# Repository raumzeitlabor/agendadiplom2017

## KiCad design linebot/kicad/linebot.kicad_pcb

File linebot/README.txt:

# LineBot

## Allgemeine Tipps

In einem sehr hellen Raum hat der Bot Schwierigkeiten, die Linien zu finden.
Deshalb etwas abdunkeln. Du kannst auch eine hellere LED einlöten. Außerdem
müssen die gemalten Linien recht breit sein. Also einen dicken Edding nehmen,
oder ein dunkles Klebeband. Der Bot hat keine Reifen, nur ein kleines Stück
Schrumpfschlauch auf den Achsen. Falls der sich gelöst hat, kommt der Bot nicht
mehr richtig um die Kurve. Dann einfach noch ein bisschen den Schrumpfschlauch
erhitzen, z.B. mit einem Feuerzeug.

## Bauanleitung

> Sicherheitshinweise
> 
> Lötzinn enthält Blei; das ist nicht gesund, wenn man es verschluckt. Wasch
> Dir deshalb nach dem Löten gründlich die Hände. Während des Arbeitens mit dem
> Lötkolben solltest Du nicht mit Lebensmitteln hantieren oder essen.
> 
> Der Lötkolben hat an seiner Spitze eine Temperatur von ca. 300 bis 350°C,
> genug um bestimmte Metalle zu schmelzen. Gib deshalb besonders Acht, Dich und
> andere nicht zu verletzen und stelle den Lötkolben immer in die Halterung,
> wenn Du ihn gerade nicht benötigst.
> 
> Halte überstehende Drahtenden fest, wenn Du sie abzwickst. So kannst Du
> vermeiden, dass die Teile wegspringen und Dich oder jemanden in Deiner
> Umgebung treffen.

Eine Platine hat normalerweise Symbole aufgedruckt, welche Bauteile man an
einer bestimmten Stelle einsetzen muss. 
Widerstände sind mit Rechtecken dargestellt und einem Wert, der mit R beginnt.
Zum Beispiel bedeutet R3: an diese Stelle gehört der Widerstand (engl.
Resistor) Nummer drei.

Die Abstände der einzelnen Kontakte haben meistens einen festen Wert, der sich
am amerikanischen Einheitensystem orientiert. Bauteile, z.B. Kondensatoren,
Widerstände, passen genau in die Platine hinein, wenn Du die Drähte mit einer
Biege-Lehre gleichmäßig umbiegst.
Damit die Teile nicht wieder herausfallen, wenn Du die Platine zum Löten
umdrehst, kannst Du die Beinchen ein wenig auseinanderbiegen.

Das Löten klappt prima, wenn Du Dich an eine einfache Reihenfolge hälst:
Lötkolben dran, Lötzinn dran, Lötzinn weg, Lötkolben weg.
Wenn Du alles richtig gemacht hast, ist das Lötzinn geschmolzen und hat um die
Kontaktstelle einen etwa kegelförmigen Hügel gebildet.

Als erstes löten wir den Elektrolytkondensator C1 auf der Unterseite der
Platine ein.
Achte darauf, das Bauteil richtig herum einzusetzen. Auf der Seite mit dem
Pluspol ist eine Kerbe, die auch auf der Platine eingezeichnet ist.
Ein Elektrolytkondensator wirkt wie eine kleine Batterie. In unserer Schaltung
ist er dazu da, Spannungsschwankungen abzufangen, wenn die Motoren anlaufen.

Nun kommt der Sockel für den Microcontroller. Er hat an einer Seite eine Kerbe,
damit man ihn richtig herum einbaut. Beginne das Löten mit einer Ecke.
Kontolliere dann, ob das Bauteil gut sitzt. Dann kommt die diagonal
gegenüberliegende Ecke dran. Wenn der Sockel fest und gerade auf der Platine
sitzt, kannst Du auch die restlichen Kontakte festlöten.
Stecke dann den Microcontroller auf den Sockel. Eine Ecke ist mit einem Punkt
markiert. Die muss dort hin, wo auf der Platine eine 1 steht.
Der Microcontroller ist ein ATTiny85. Er ist das Gehirn unseres Roboters. Dort
kommen die Messwerte aus den Sensoren an und die Motoren bekommen von dort ihre
Steuersignale.

Jetzt löten wir alle fünf Widerstände fest. Die Richtung ist bei einem
Widerstand nicht wichtig aber der Wert muss stimmen. Jeder Widerstand hat einen
Code aus farbigen Ringen aufgedruckt. Achte darauf, dass Du die Widerstände in
Deinem Roboter-Bausatz nicht durcheinander bringst. Wenn Du Dir nicht sicher
bist, kannst Du den Wert des Widerstandes mit dem Multimeter nachmessen.
Widerstände sind zum Beispiel dazu da, den Strom in der Schaltung zu begrenzen,
damit andere Bauteile nicht kaputt gehen.

Die zwei kleinen Dioden sind als nächstes dran. Diesmal ist es wichtig, sie
richtig herum einzubauen. Dafür haben sie auf einer Seite einen schwarzen
Strich. In unserer Schaltung sind sie dafür zuständig, die Spannung der Motoren
abzufangen, die den Rest der Schaltung durcheinanderbringen würde.

Nun kommen die Transistoren dran. Sie haben eine flache und eine runde Seite,
damit man weiß, wie man sie einbauen muss. Die Beinchen der Transistoren sind
sehr dicht zusammen. Gib darauf acht, dass Du die Kontakte auf der Platine
nicht mit zu viel Lötzinn verbindest.
Transistoren funktionieren wie eine Schleuse: Wenn an der Basis (hier in der
Mitte) ein kleiner Steuerstrom anliegt, dann öffnen sie die Verbindung und
lassen den Strom durch. Wir brauchen Sie zum Ansteuern der Motoren.

Der Schalter hat drei Kontakte in der Mitte, die Du anlöten musst. Die beiden
Pfosten helfen, dass der Schalter besser auf der Platine hält und Du musst Sie
nicht anlöten.
Mit dem Schalter kannst Du den Bot ausschalten, wenn Du ihn gerade nicht auf
Liniensuche schicken willst.

Die Leuchtdiode (LED - Light Emitting Diode) kommt auf die Unterseite der
Platine. Sie funktioniert nur, wenn Du sie richtig herum einbaust. Die
abgeflachte Seite der LED ist eingezeichnet. Jetzt wird es ein bisschen
komplizierter. Die beiden Fototransistoren haben auch eine flache Seite. Sie
werden aber nicht direkt eingesetzt, sondern mit einer Halterung, die genau
darüber passt. Achte darauf, dass die Fototransistoren richtig herum sind und
drücke sie ganz in das Gehäuse hinein, bevor Du alles anlötest. Die Beinchen
der Transistoren kannst Du abzwicken. Aber wirf sie nicht weg, wir brauchen sie
im nächsten Schritt.
Die Fototransistoren sind der Sensor unseres Roboters. Sie lassen mehr Strom
durch, wenn mehr Licht einfällt. Das Licht kommt in diesem Fall von der LED und
wird dann von der Oberfläche des Tisches reflektiert. Eine dunkle Linie
reflektiert nicht so viel Licht und wird deshalb von den Sensoren erkannt.

Als Antrieb für unseren Roboter dienen zwei kleine Elektromotoren. Zur Montage
schiebst Du sie in die Halterung aus Kunststoff, bedruckte Seite in Richtung
Schlitz. Die Kontaktbeinchen kommen durch die Ösen der Halterung und werden
direkt am Motor angelötet. Biege die Kontakte so, dass sie senkrecht zur
Bodenfläche stehen und löte die Motoren auf der Platine fest.
Die Motoren sind sehr klein und haben nur ein geringes Drehmoment. Deshalb
bekommt unser Bot keine großen Reifen.

Als letztes wird die Batteriehalterung angelötet. Wenn Du nun die Batterien
einsetzt und den Schalter anstellst sollte der Bot losfahren. Viel Spaß!

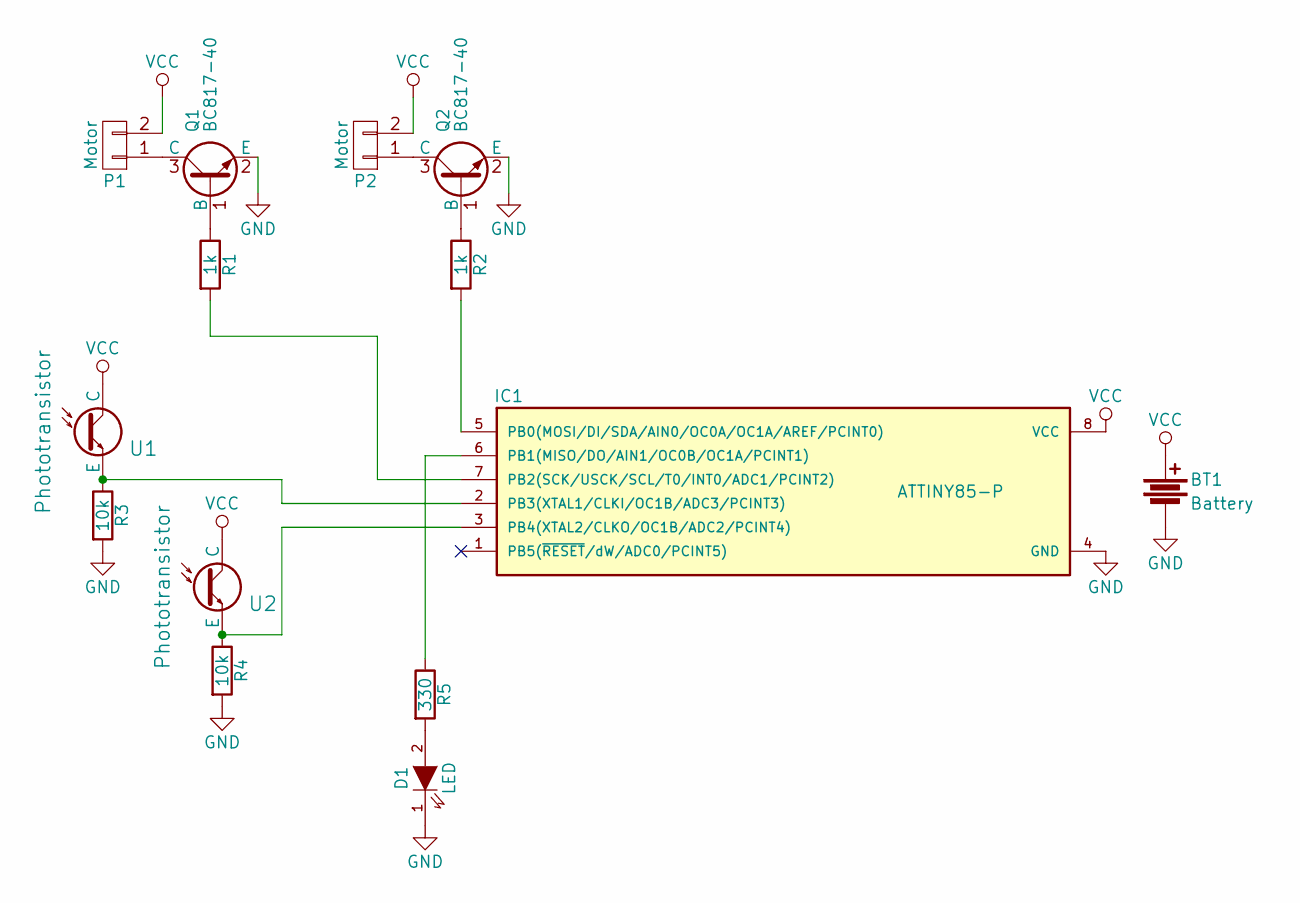
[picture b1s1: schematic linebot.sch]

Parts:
BT1: Battery; batteryholder_AAAx2
D1: LED; LED-5MM
IC1: ATTINY85-P; DIP-8_W7.62mm
P1, P2: Motor; motorholder
Q1, Q2: BC817-40; TO-92_Inline_Narrow_Oval
R1, R2: 1k; Resistor_Horizontal_RM10mm
R3, R4: 10k; Resistor_Horizontal_RM10mm
R5: 330; Resistor_Horizontal_RM10mm
U1, U2: Phototransistor; LED-5MM

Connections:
GND: BT1.2, D1.1 (K), IC1.4 (GND), Q1.2 (E), Q2.2 (E), R3.2, R4.2
unnamed: D1.2 (A), R5.2
unnamed: IC1.2 (PB3(XTAL1/CLKI/OC1B/ADC3/PCINT3)), R3.1, U1.2 (E)
unnamed: IC1.3 (PB4(XTAL2/CLKO/OC1B/ADC2/PCINT4)), R4.1, U2.2 (E)
unnamed: IC1.5 (PB0(MOSI/DI/SDA/AIN0/OC0A/OC1A/AREF/PCI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), R2.2
unnamed: IC1.6 (PB1(MISO/DO/AIN1/OC0B/OC1A/PCINT1)), R5.1
unnamed: IC1.7 (PB2(SCK/USCK/SCL/T0/INT0/ADC1/PCINT2)), R1.2
unnamed: P1.1, Q1.3 (C)
unnamed: P2.1, Q2.3 (C)
unnamed: Q1.1 (B), R1.1
unnamed: Q2.1 (B), R2.1
VCC: BT1.1, IC1.8 (VCC), P1.2, P2.2, U1.1 (C), U2.1 (C)

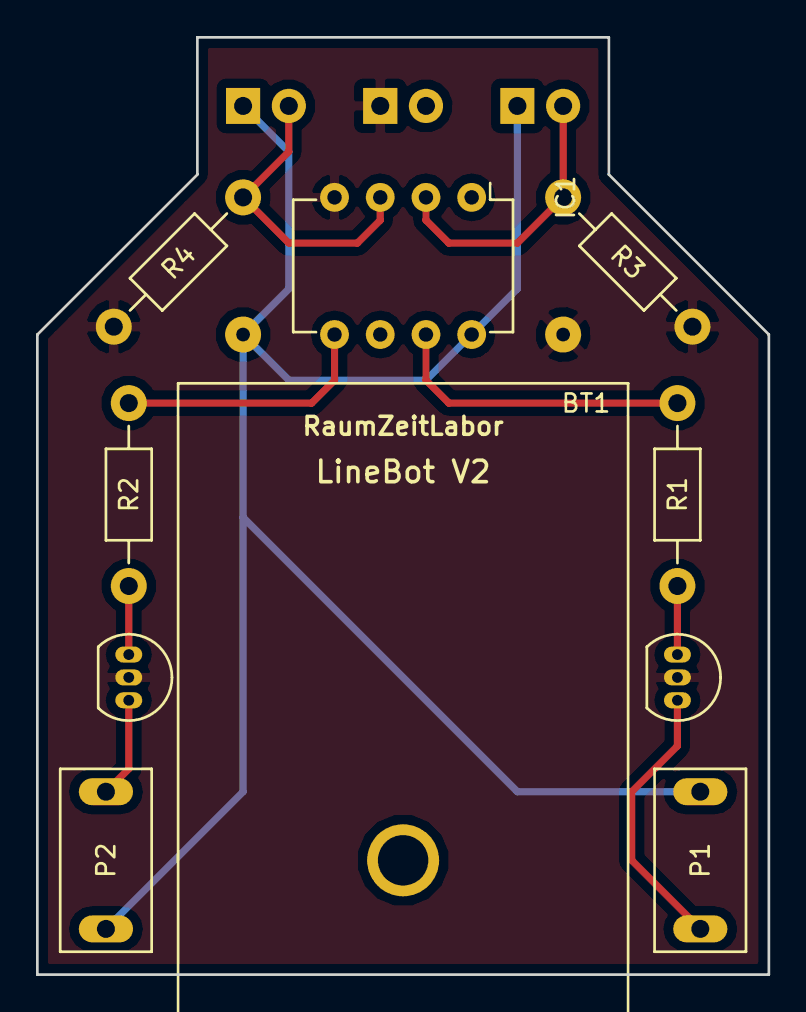
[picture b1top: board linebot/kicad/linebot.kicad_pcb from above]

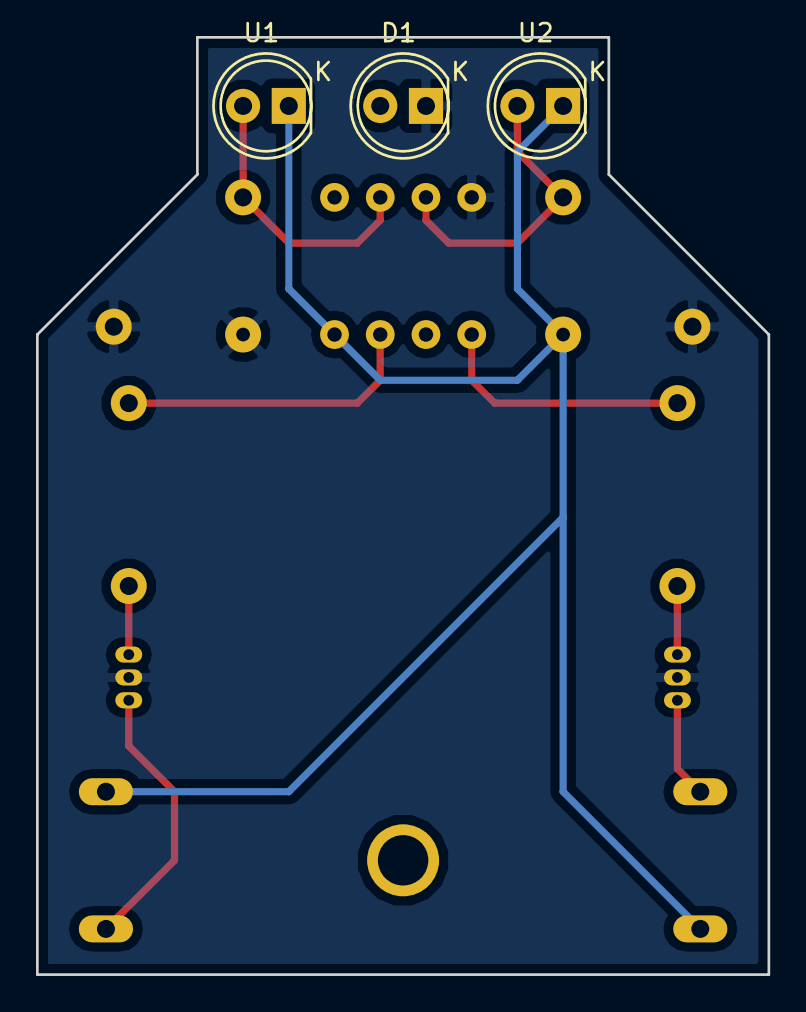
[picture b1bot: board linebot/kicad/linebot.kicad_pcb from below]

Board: 2 copper layers, 40.6 x 52.1 mm, 13 parts (3 on the bottom side), 10 nets.

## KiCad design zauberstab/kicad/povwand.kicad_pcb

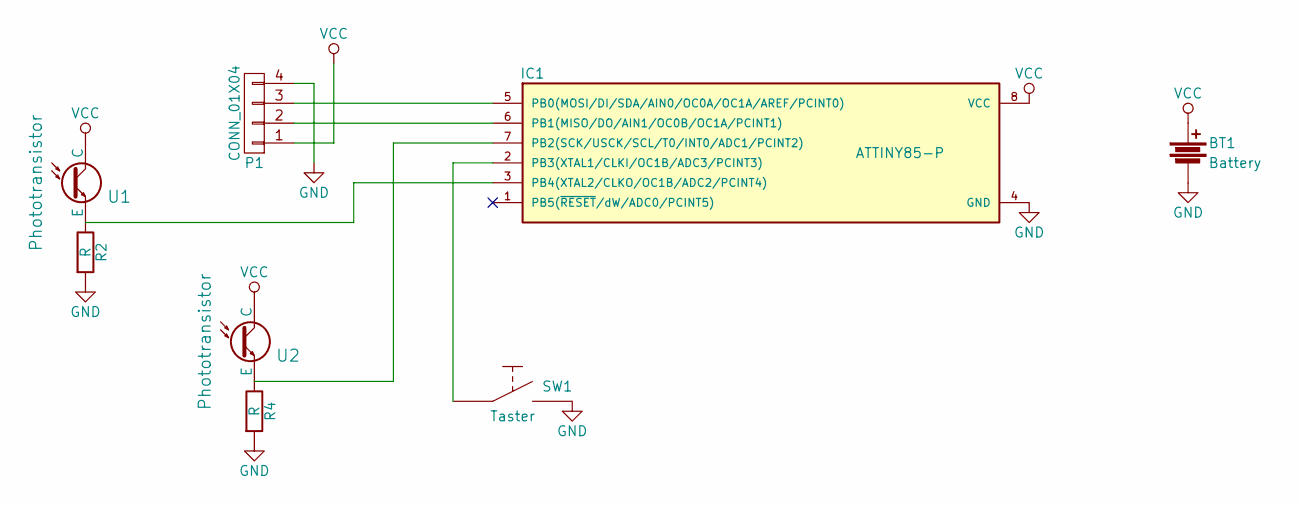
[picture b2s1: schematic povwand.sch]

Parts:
BT1: Battery; 2xAAAbattery_holder_long
IC1: ATTINY85-P; DIP-8_W7.62mm
P1: CONN_01X04; APA102x8
R2, R4: R; Resistor_Horizontal_RM10mm
SW1: Taster; Kurzhubtaster
U1, U2: Phototransistor; LED-5MM

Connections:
GND: BT1.2, IC1.4 (GND), P1.4, R2.2, R4.2, SW1.2
unnamed: IC1.2 (PB3(XTAL1/CLKI/OC1B/ADC3/PCINT3)), SW1.1
unnamed: IC1.3 (PB4(XTAL2/CLKO/OC1B/ADC2/PCINT4)), R2.1, U1.2 (E)
unnamed: IC1.5 (PB0(MOSI/DI/SDA/AIN0/OC0A/OC1A/AREF/PCI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), P1.3
unnamed: IC1.6 (PB1(MISO/DO/AIN1/OC0B/OC1A/PCINT1)), P1.2
unnamed: IC1.7 (PB2(SCK/USCK/SCL/T0/INT0/ADC1/PCINT2)), R4.1, U2.2 (E)
VCC: BT1.1, IC1.8 (VCC), P1.1, U1.1 (C), U2.1 (C)

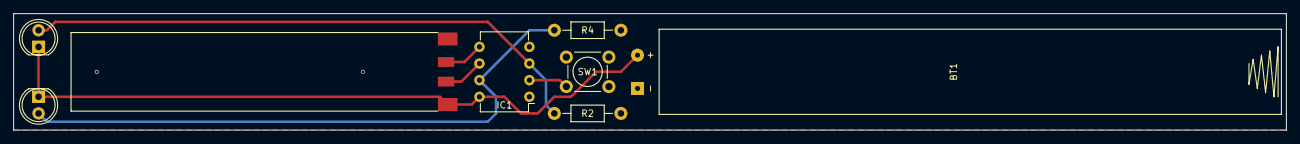
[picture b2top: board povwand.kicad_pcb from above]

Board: 2 copper layers, 194.3 x 17.8 mm, 8 parts (0 on the bottom side), 7 nets.

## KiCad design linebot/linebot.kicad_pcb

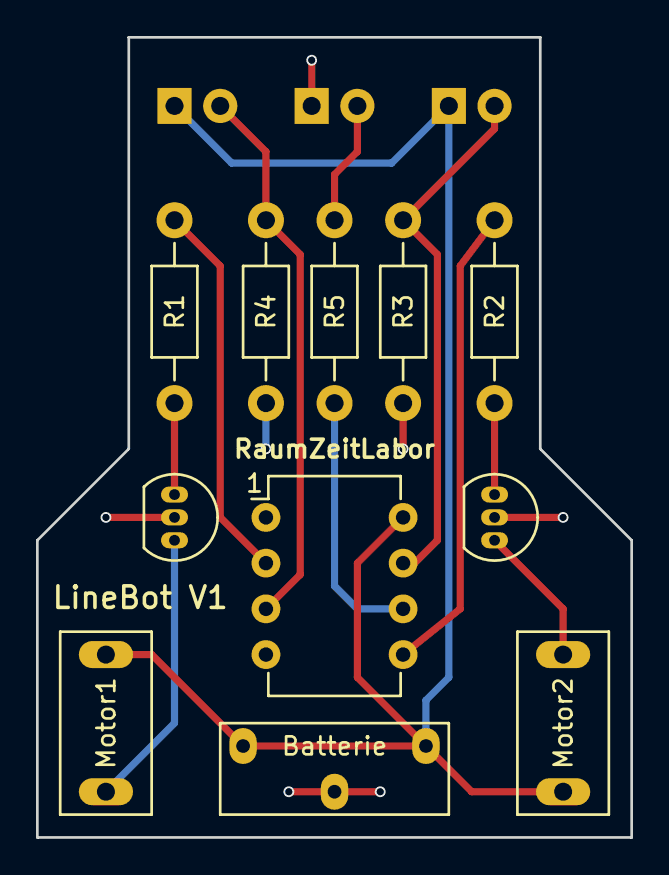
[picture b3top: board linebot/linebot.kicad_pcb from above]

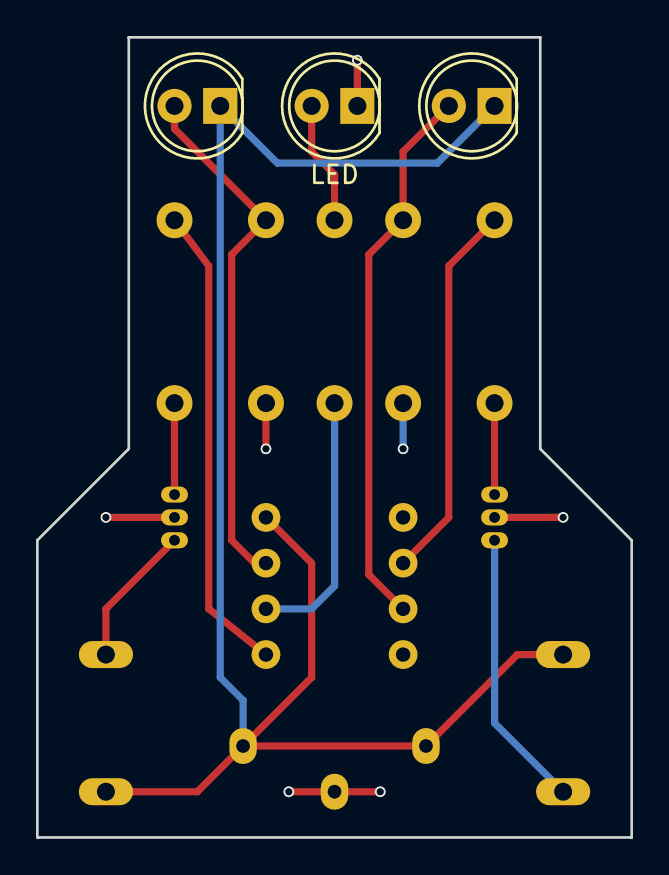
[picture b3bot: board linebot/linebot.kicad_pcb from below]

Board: 2 copper layers, 33.0 x 44.4 mm, 14 parts (3 on the bottom side), 12 nets.

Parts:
1: ATTINY85-P; DIP-8_W7.62mm
Batterie: Battery; Batterie_aufrecht
LED: LED; LED-5MM
Motor1, Motor2: Motor; motorholder
Q1, Q2: BC817-40; TO-92_Inline_Narrow_Oval
Q3, Q4: PT; LED-5MM
R1, R2: 1k; Resistor_Horizontal_RM10mm
R3, R4: 10k; Resistor_Horizontal_RM10mm
R5: 330; Resistor_Horizontal_RM10mm

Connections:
GND: 1.4, Batterie.2, LED.1, Q1.2, Q2.2, R3.2, R4.2
unnamed: LED.2, R5.2
unnamed: 1.2, R1.2
unnamed: 1.3, Q4.2, R4.1
unnamed: 1.5, R2.2
unnamed: 1.6, R5.1
unnamed: 1.7, Q3.2, R3.1
unnamed: Motor1.1, Q1.3
unnamed: Motor2.1, Q2.3
unnamed: Q1.1, R1.1
unnamed: Q2.1, R2.1
VCC: 1.8, Batterie.1, Motor1.2, Motor2.2, Q3.1, Q4.1

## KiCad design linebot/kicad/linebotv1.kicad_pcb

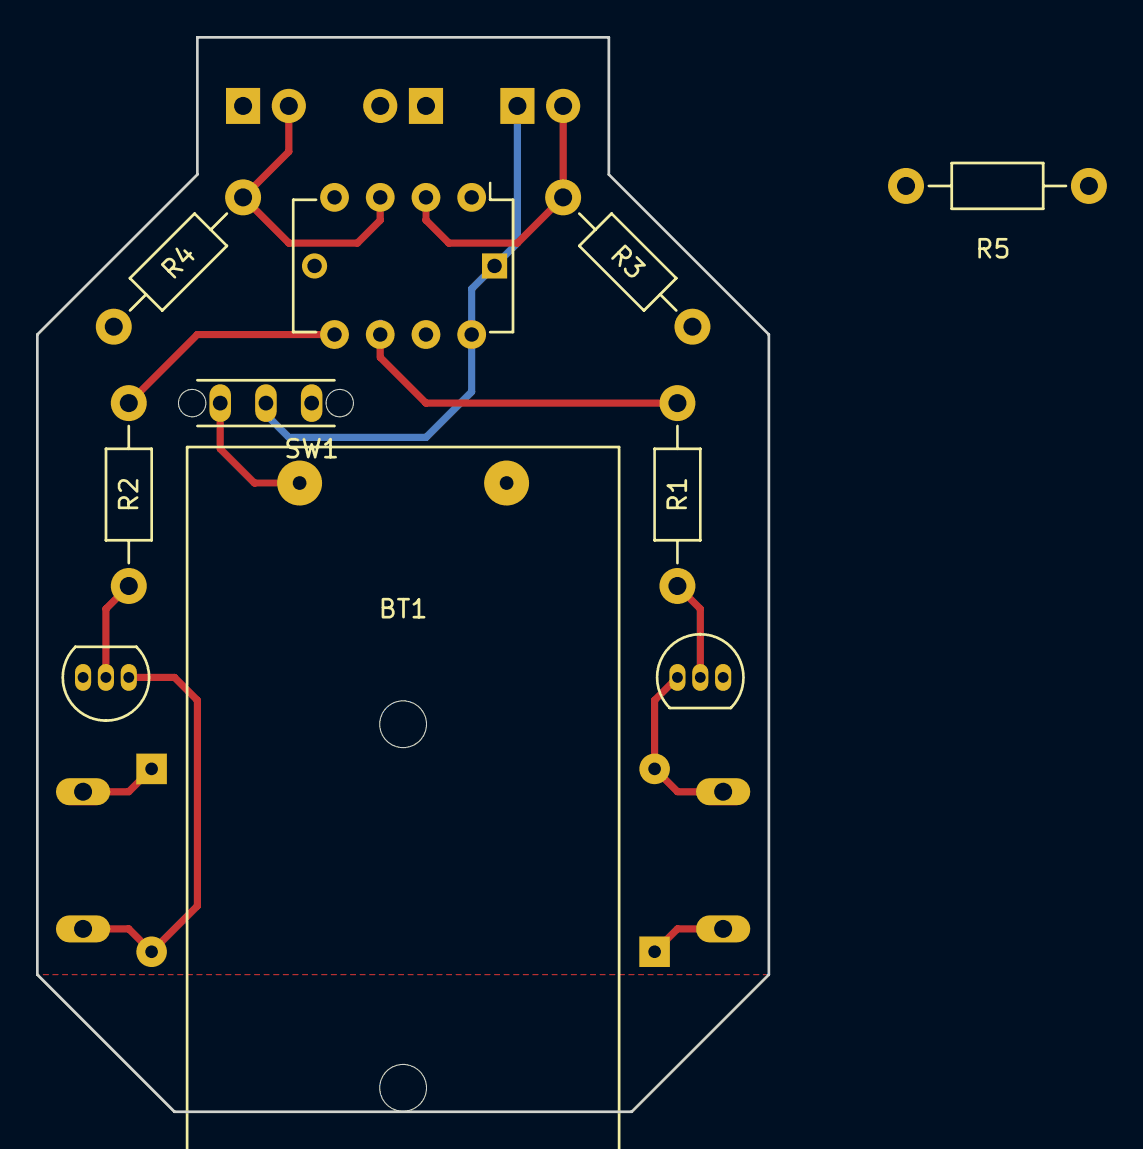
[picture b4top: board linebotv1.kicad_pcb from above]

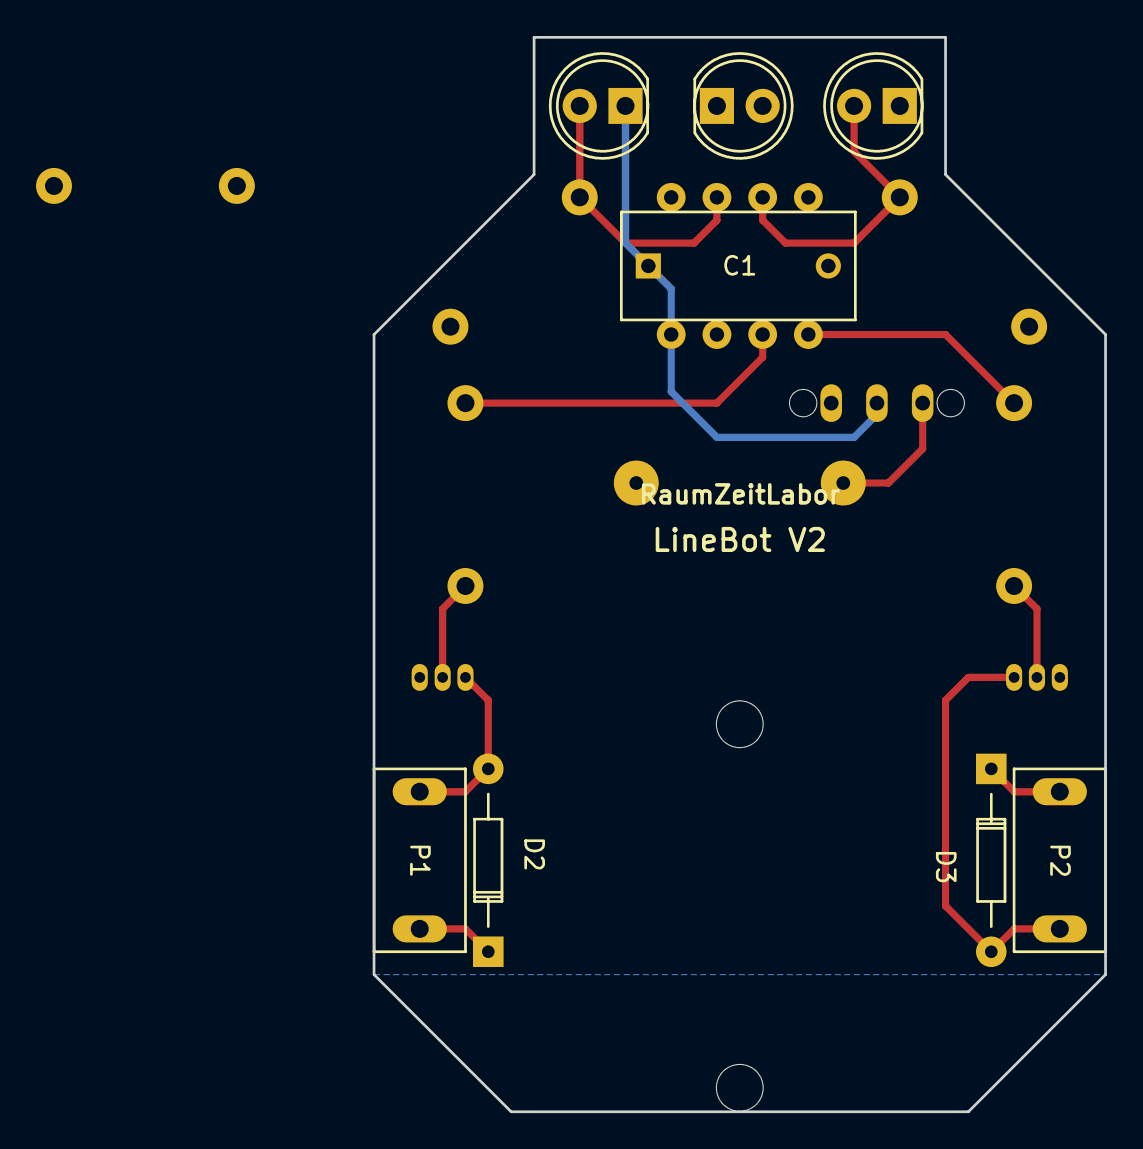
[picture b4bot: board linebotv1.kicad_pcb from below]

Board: 2 copper layers, 40.6 x 59.7 mm, 18 parts (8 on the bottom side), 13 nets.

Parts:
BT1: Battery; batteryholder_AAAx2
C1: 10u; C_Rect_L13_W6_H12_P10
D1: LED; LED-5MM
D2, D3: 1N4148; Diode_DO-35_SOD27_Horizontal_RM10
IC1: ATTINY85-P; DIP-8_W7.62mm
P1, P2: Motor; motorholder
R1, R2: 1k; Resistor_Horizontal_RM10mm
R3, R4: 10k; Resistor_Horizontal_RM10mm
R5: 220; Resistor_Horizontal_RM10mm
SW1: Switch; Schiebeschalter
U1, U2: Phototransistor; LED-5MM
U3, U4: BC337; BC337_narrow

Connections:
GND: BT1.2, C1.2, D1.1, IC1.4, R3.2, R4.2, U3.3, U4.3
unnamed: BT1.1, SW1.1
unnamed: D1.2, R5.2
unnamed: D2.2, P1.1, U3.1
unnamed: D3.2, P2.1, U4.1
unnamed: IC1.2, R3.1, U1.2
unnamed: IC1.3, R4.1, U2.2
unnamed: IC1.5, R2.2
unnamed: IC1.6, R1.2
unnamed: IC1.7, R5.1
unnamed: R1.1, U3.2
unnamed: R2.1, U4.2
VCC: C1.1, D2.1, D3.1, IC1.8, P1.2, P2.2, SW1.2, U1.1, U2.1

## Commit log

2017-02-20 First commit
    Die Hardware für einen einfachen Line Follower Bot
2017-02-20 Ordner umbenannt
2017-03-02 Added second project
2017-03-27 Boards updated
2017-03-27 Added 3D prints
2017-04-02 images added
2017-04-13 neues Bild
2017-10-07 software update
2020-12-18 linebot: README.txt ergänzt
    Das Readme beinhaltet die Hinweise und die Aufbauanleitung, die vor kurzem
    nochmal über die RZL Mailingliste gesendet wurde.
